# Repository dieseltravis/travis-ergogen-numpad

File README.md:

# travis-ergogen-numpad
A numpad made with Ergogen v4 and SMD components. *Alpha* quality!

## Parts ##

JLCPCB PCBA:
* 17 @ C5184526 Kailh CPG151101S11-1 Mechanical Keyboard Shaft ROHS https://jlcpcb.com/partdetail/Kailh-CPG151101S111/C5184526
* 18 @ C7420318 hongjiacheng 1N4148W SOD-123 Switching Diode ROHS https://jlcpcb.com/partdetail/hongjiacheng-1N4148W/C7420318
* 21 @ C5149201 OPSCO Optoelectronics SK6812MINI-E SMD RGB LEDs(Built-in IC) ROHS https://jlcpcb.com/partdetail/OPSCOOptoelectronics-SK6812MINIE/C5149201
* 21 @ C710467 HUI JU NM1206B104K251CEGN 100nF X7R ±10% 1206 Multilayer Ceramic Capacitors MLCC - SMD/SMT ROHS https://jlcpcb.com/partdetail/HUIJU-NM1206B104K251CEGN/C710467
* C4747954 KNSCHA RST470UF10V029 470uF 10V 260mA@120Hz ±20% SMD,D6.3xL7.7mm Aluminum Electrolytic Capacitors - SMD ROHS https://jlcpcb.com/partdetail/KNSCHA-RST470UF10V029/C4747954

Aliexpress:
* Rotary encoder: EC11 12.5mm 5pcs https://www.aliexpress.us/item/2251832789732148.html
* RP2040 Pro Micro 16M https://www.aliexpress.us/item/3256805943704472.html
* 0.91 Inch OLED Module 0.91" White Blue 128X32 https://www.aliexpress.us/item/3256805787666312.html

Adafruit:
* 2 @ Kailh Mechanical Key Switches - Tactile Brown - 10 pack - Cherry MX Brown Compatible https://www.adafruit.com/product/4954
* Woven USB Cable with USB A to Right Angle USB C https://www.adafruit.com/product/5031

## References ##

* [sadekbaroudi's QMK RGB Matrix configuration](https://github.com/sadekbaroudi/keyboard-guides/blob/master/firmware/qmk/RGB_MATRIX/RGB_MATRIX.md)
* [my first KB](https://github.com/dieseltravis/travis-ergogen-2024/)

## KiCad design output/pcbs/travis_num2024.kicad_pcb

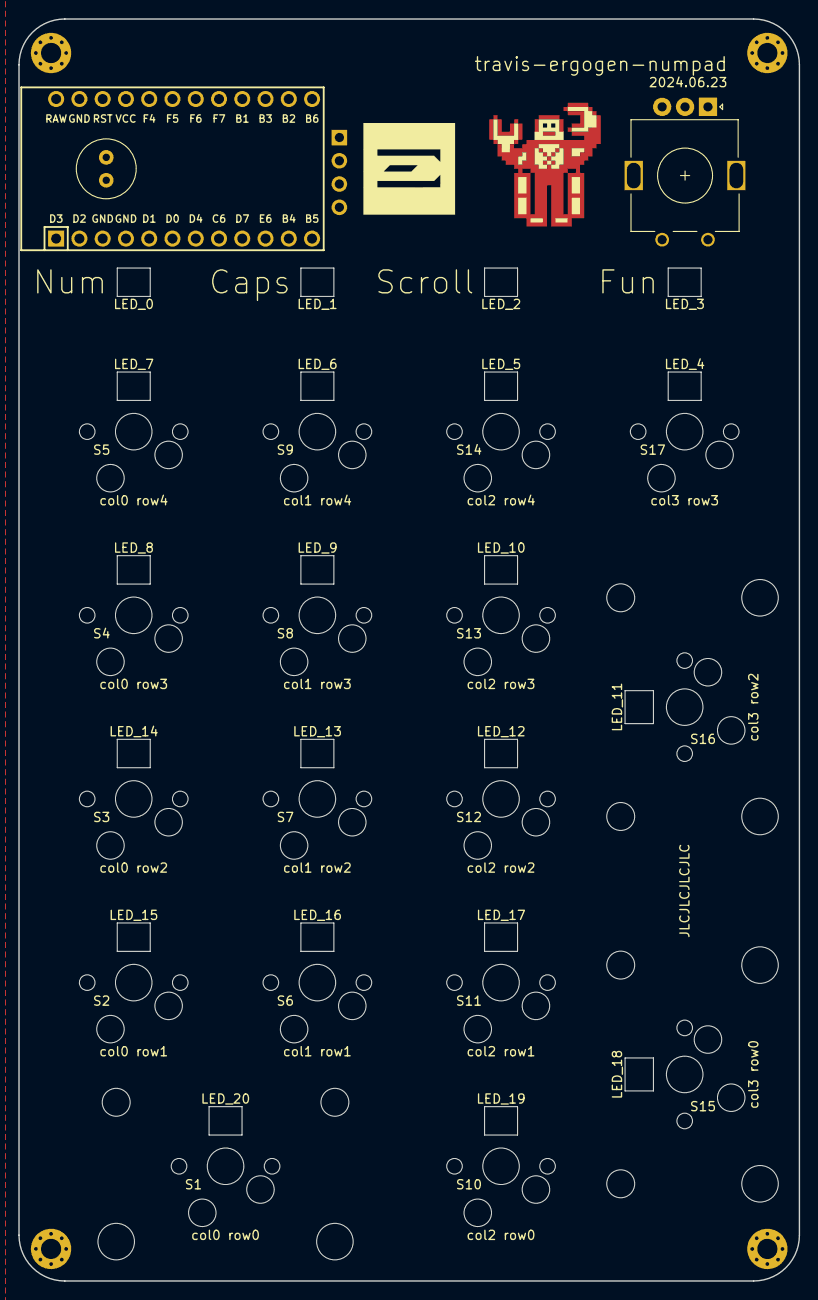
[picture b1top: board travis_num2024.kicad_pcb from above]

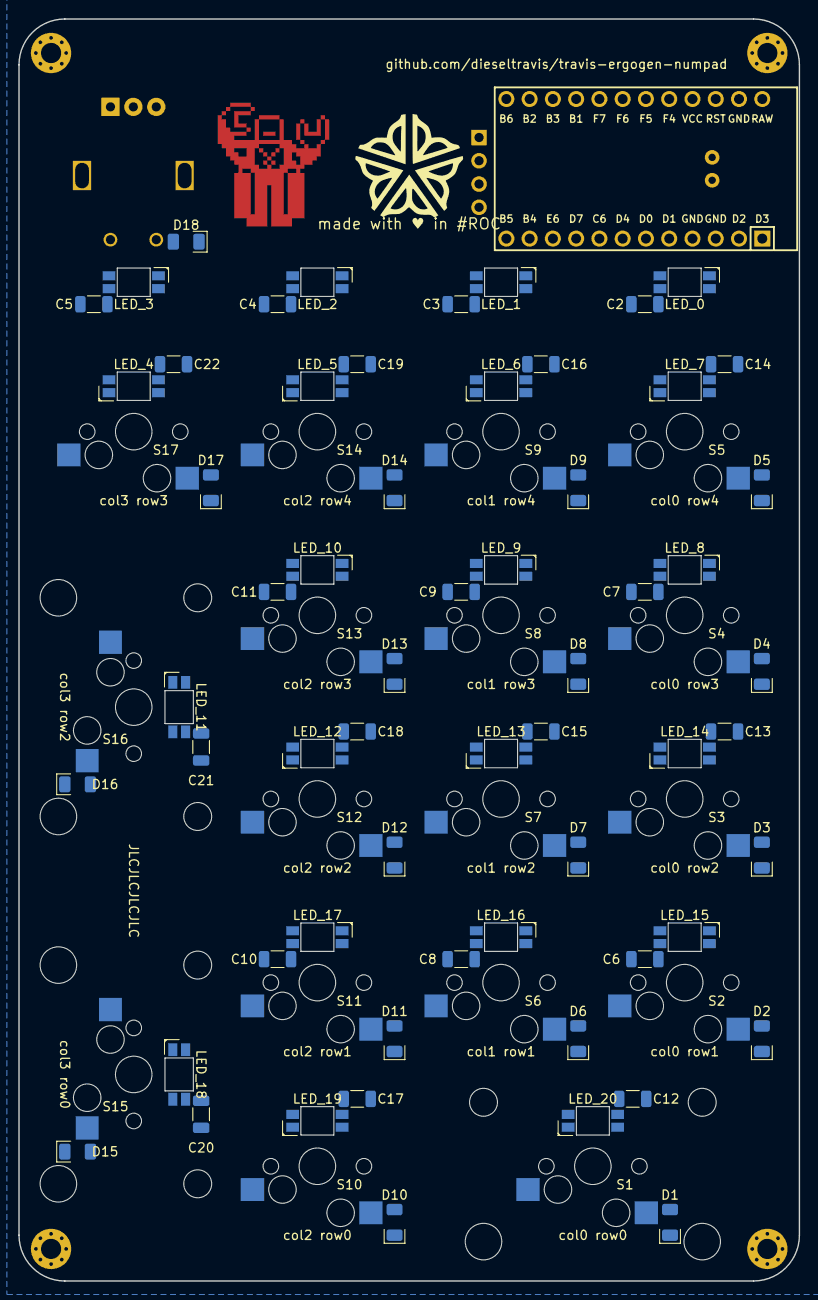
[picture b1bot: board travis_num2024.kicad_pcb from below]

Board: 2 copper layers, 85.2 x 137.8 mm, 91 parts (61 on the bottom side), 54 nets, no tracks yet.

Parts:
C1: 6.3V 1000uF; C_Radial_D6.3mm_H11.0mm_P2.50mm
C2, C3, C4, C5, C6, C7, C8, C9, C10, C11, C12, C13, C14, C15, C16, C17, C18, C19, C20, C21, C22: C_1206_3216Metric
D1, D2, D3, D4, D5, D6, D7, D8, D9, D10, D11, D12, D13, D14, D15, D16, D17, D18: D_1206_3216Metric
HOLE1, HOLE2, HOLE3, HOLE4: MountingHole_2.2mm_M2_Pad_Via
LED1, LED2, LED3, LED4, LED5, LED6, LED7, LED8, LED9, LED10, LED11, LED12, LED13, LED14, LED15, LED16, LED17, LED18, LED19, LED20, LED21: SK6812mini-e; led_SK6812mini-e (per-key, single-side)
LOGO1: utility_ergogen_logo
LOGO2: travis
MCU1: Arduino Pro Micro; Arduino_Pro_Micro
OLED1: OLED; OLED_headers
ROC1: travis
ROT1: EC11; ec11
S1, S2, S3, S4, S5, S6, S7, S8, S9, S10, S11, S12, S13, S14, S15, S16, S17: Kailh MX Switch Sockets; MX
STAB2u1, STAB2u2, STAB2u3: Stabilizer_MX_2.00u

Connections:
GND: C1.2, C2.2, C3.2, C4.2, C5.2, C6.2, C7.2, C8.2, C9.2, C10.2, C11.2, C12.2, C13.2, C14.2, C15.2, C16.2, C17.2, C18.2, C19.2, C20.2, C21.2, C22.2, LED1.3, LED2.3, LED3.3, LED4.3, LED5.3, LED6.3, LED7.3, LED8.3, LED9.3, LED10.3, LED11.3, LED12.3, LED13.3, LED14.3, LED15.3, LED16.3, LED17.3, LED18.3, LED19.3, LED20.3, LED21.3, MCU1.3, MCU1.4, MCU1.23, OLED1.1, ROT1.B
LED_0: LED1.4, MCU1.12
LED_1: LED1.2, LED2.4
LED_2: LED2.2, LED3.4
LED_3: LED3.2, LED4.4
LED_4: LED4.2, LED21.4
LED_5: LED18.4, LED21.2
LED_6: LED15.4, LED18.2
LED_7: LED13.4, LED15.2
LED_8: LED6.4, LED13.2
LED_9: LED6.2, LED8.4
LED_10: LED8.2, LED10.4
LED_11: LED10.2, LED20.4
LED_12: LED17.4, LED20.2
LED_13: LED14.4, LED17.2
LED_14: LED12.4, LED14.2
LED_15: LED5.4, LED12.2
LED_16: LED5.2, LED7.4
LED_17: LED7.2, LED9.4
LED_18: LED9.2, LED19.4
LED_19: LED16.4, LED19.2
LED_20: LED11.4, LED16.2
VCC: C1.1, C2.1, C3.1, C4.1, C5.1, C6.1, C7.1, C8.1, C9.1, C10.1, C11.1, C12.1, C13.1, C14.1, C15.1, C16.1, C17.1, C18.1, C19.1, C20.1, C21.1, C22.1, LED1.1, LED2.1, LED3.1, LED4.1, LED5.1, LED6.1, LED7.1, LED8.1, LED9.1, LED10.1, LED11.1, LED12.1, LED13.1, LED14.1, LED15.1, LED16.1, LED17.1, LED18.1, LED19.1, LED20.1, LED21.1, MCU1.21, OLED1.2
col0: MCU1.20, S1.1, S2.1, S3.1, S4.1, S5.1
col1: MCU1.19, S6.1, S7.1, S8.1, S9.1
col2: MCU1.18, S10.1, S11.1, S12.1, S13.1, S14.1
col3: MCU1.17, ROT1.1, S15.1, S16.1, S17.1
encA: MCU1.14, ROT1.A
encC: MCU1.13, ROT1.C
enc_to: D18.2, ROT1.2
matrix_col0_row0: D1.2, S1.2
matrix_col0_row1: D2.2, S2.2
matrix_col0_row2: D3.2, S3.2
matrix_col0_row3: D4.2, S4.2
matrix_col0_row4: D5.2, S5.2
matrix_col1_row1: D6.2, S6.2
matrix_col1_row2: D7.2, S7.2
matrix_col1_row3: D8.2, S8.2
matrix_col1_row4: D9.2, S9.2
matrix_col2_row0: D10.2, S10.2
matrix_col2_row1: D11.2, S11.2
matrix_col2_row2: D12.2, S12.2
matrix_col2_row3: D13.2, S13.2
matrix_col2_row4: D14.2, S14.2
matrix_col3_row0: D15.2, S15.2
matrix_col3_row2: D16.2, S16.2
matrix_col3_row4: D17.2, S17.2
row0: D1.1, D10.1, D15.1, MCU1.7
row1: D2.1, D6.1, D11.1, MCU1.8
row2: D3.1, D7.1, D12.1, D16.1, MCU1.9
row3: D4.1, D8.1, D13.1, D17.1, MCU1.10
row4: D5.1, D9.1, D14.1, D18.1, MCU1.11
scl: MCU1.6, OLED1.3
sda: MCU1.5, OLED1.4

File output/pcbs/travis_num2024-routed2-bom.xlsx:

Id | Designator | Footprint | Quantity | Designation | JLCPCB Part #（optional）
1 | S5,S14,S2,S17,S3,S8,S15,S6,S11,S12,S1,S9,S10,S7,S13,S16,S4 | MX | 17 | Kailh MX Switch Sockets | C5184526
7 | LED_0,LED_12,LED_5,LED_17,LED_3,LED_15,LED_2,LED_1,LED_7,LED_19,LED_18,LED_8,LE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 | led_SK6812mini-e (per-key, single-side) | 21 | SK6812mini-e | C5149201
8 | C14,C2,C21,C13,C5,C17,C3,C20,C9,C15,C11,C8,C7,C16,C10,C18,C4,C19,C22,C12,C6 | C_1206_3216Metric | 21 | C_1206_3216Metric | C710467
9 | D3,D18,D14,D6,D17,D8,D1,D16,D12,D2,D13,D4,D10,D9,D15,D5,D11,D7 | D_1206_3216Metric | 18 | D_1206_3216Metric | C7420318

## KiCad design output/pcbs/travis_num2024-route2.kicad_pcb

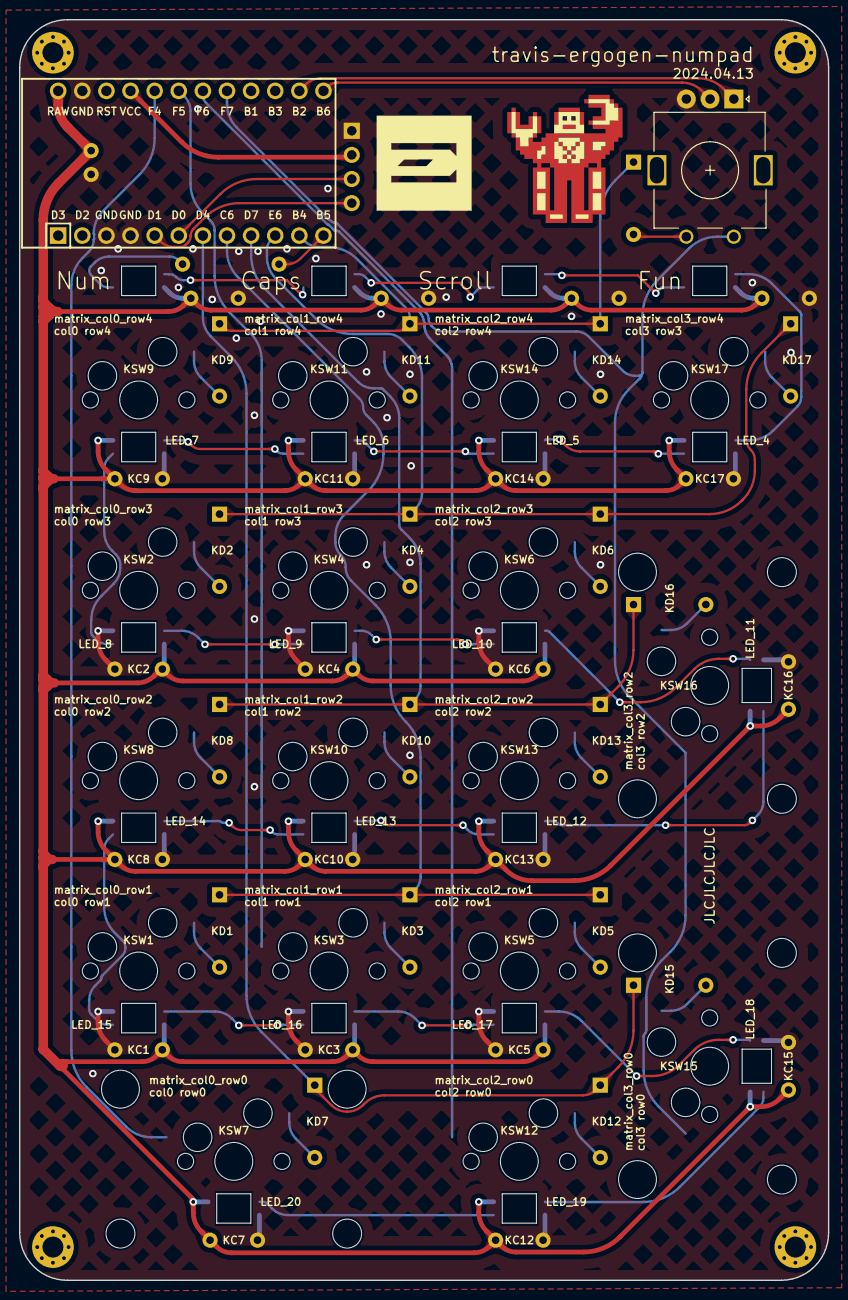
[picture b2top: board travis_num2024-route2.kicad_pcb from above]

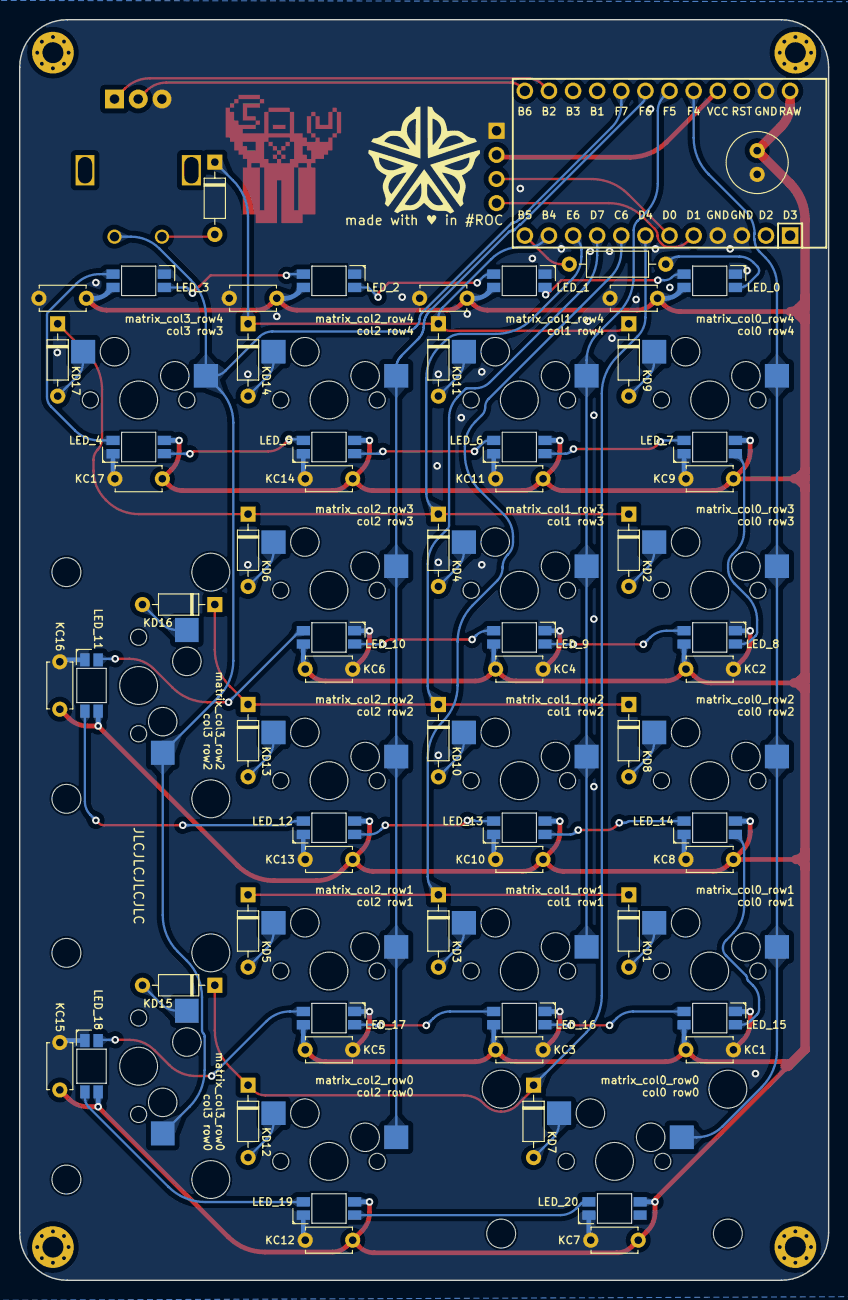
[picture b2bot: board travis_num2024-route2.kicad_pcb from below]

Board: 2 copper layers, 85.2 x 132.8 mm, 92 parts (63 on the bottom side), 56 nets.

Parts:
C1: 6.3V 1000uF; C_Radial_D6.3mm_H11.0mm_P2.50mm
C2, C3, C4, C5: 104; C_Disc_D4.7mm_W2.5mm_P5.00mm
D1: 1N4148; Diode_DO-35
HOLE1, HOLE2, HOLE3, HOLE4: MountingHole_2.2mm_M2_Pad_Via
KC1, KC2, KC3, KC4, KC5, KC6, KC7, KC8, KC9, KC10, KC11, KC12, KC13, KC14, KC15, KC16, KC17: 104; C_Disc_D4.7mm_W2.5mm_P5.00mm
KD1, KD2, KD3, KD4, KD5, KD6, KD7, KD8, KD9, KD10, KD11, KD12, KD13, KD14, KD15, KD16, KD17: 1N4148; Diode_DO-35
KSW1, KSW2, KSW3, KSW4, KSW5, KSW6, KSW7, KSW8, KSW9, KSW10, KSW11, KSW12, KSW13, KSW14, KSW15, KSW16, KSW17: Kailh MX Switch Sockets; MX
LED1, LED2, LED3, LED4: SK6812mini-e; led_SK6812mini-e (per-key, single-side)
LED_4-row3-col3, LED_5-row4-col2, LED_6-row4-col1, LED_7-row4-col0, LED_8-row3-col0, LED_9-row3-col1, LED_10-row3-col2, LED_11-row2-col3, LED_12-row2-col2, LED_13-row2-col1, LED_14-row2-col0, LED_15-row1-col0, LED_16-row1-col1, LED_17-row1-col2, LED_18-row0-col3, LED_19-row0-col2, LED_20-row0-col0: SK6812mini-e; led_SK6812mini-e
LOGO1: ergogen_logo
LOGO2: travis
MCU1: Arduino Pro Micro; Arduino_Pro_Micro
OLED1: OLED; OLED_headers
R1: 470R; R_Axial_DIN0207_L6.3mm_D2.5mm_P10.16mm_Horizontal
ROC1: travis
ROT1: EC11; ec11
STAB2u1, STAB2u2, STAB2u3: Stabilizer_MX_2.00u

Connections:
GND: C1.2, C2.2, C3.2, C4.2, C5.2, KC1.2, KC2.2, KC3.2, KC4.2, KC5.2, KC6.2, KC7.2, KC8.2, KC9.2, KC10.2, KC11.2, KC12.2, KC13.2, KC14.2, KC15.2, KC16.2, KC17.2, LED1.3, LED2.3, LED3.3, LED4.3, LED_4-row3-col3.3, LED_5-row4-col2.3, LED_6-row4-col1.3, LED_7-row4-col0.3, LED_8-row3-col0.3, LED_9-row3-col1.3, LED_10-row3-col2.3, LED_11-row2-col3.3, LED_12-row2-col2.3, LED_13-row2-col1.3, LED_14-row2-col0.3, LED_15-row1-col0.3, LED_16-row1-col1.3, LED_17-row1-col2.3, LED_18-row0-col3.3, LED_19-row0-col2.3, LED_20-row0-col0.3, MCU1.3, MCU1.4, MCU1.23, OLED1.1, ROT1.B
LED: MCU1.12, R1.1
LED_0: LED1.4, R1.2
LED_1: LED1.2, LED2.4
LED_2: LED2.2, LED3.4
LED_3: LED3.2, LED4.4
LED_4: LED4.2, LED_4-row3-col3.4
LED_5: LED_4-row3-col3.2, LED_5-row4-col2.4
LED_6: LED_5-row4-col2.2, LED_6-row4-col1.4
LED_7: LED_6-row4-col1.2, LED_7-row4-col0.4
LED_8: LED_7-row4-col0.2, LED_8-row3-col0.4
LED_9: LED_8-row3-col0.2, LED_9-row3-col1.4
LED_10: LED_9-row3-col1.2, LED_10-row3-col2.4
LED_11: LED_10-row3-col2.2, LED_11-row2-col3.4
LED_12: LED_11-row2-col3.2, LED_12-row2-col2.4
LED_13: LED_12-row2-col2.2, LED_13-row2-col1.4
LED_14: LED_13-row2-col1.2, LED_14-row2-col0.4
LED_15: LED_14-row2-col0.2, LED_15-row1-col0.4
LED_16: LED_15-row1-col0.2, LED_16-row1-col1.4
LED_17: LED_16-row1-col1.2, LED_17-row1-col2.4
LED_18: LED_17-row1-col2.2, LED_18-row0-col3.4
LED_19: LED_18-row0-col3.2, LED_19-row0-col2.4
LED_20: LED_19-row0-col2.2, LED_20-row0-col0.4
RAW: C1.1, C2.1, C3.1, C4.1, C5.1, KC1.1, KC2.1, KC3.1, KC4.1, KC5.1, KC6.1, KC7.1, KC8.1, KC9.1, KC10.1, KC11.1, KC12.1, KC13.1, KC14.1, KC15.1, KC16.1, KC17.1, LED1.1, LED2.1, LED3.1, LED4.1, LED_4-row3-col3.1, LED_5-row4-col2.1, LED_6-row4-col1.1, LED_7-row4-col0.1, LED_8-row3-col0.1, LED_9-row3-col1.1, LED_10-row3-col2.1, LED_11-row2-col3.1, LED_12-row2-col2.1, LED_13-row2-col1.1, LED_14-row2-col0.1, LED_15-row1-col0.1, LED_16-row1-col1.1, LED_17-row1-col2.1, LED_18-row0-col3.1, LED_19-row0-col2.1, LED_20-row0-col0.1, MCU1.24
VCC: MCU1.21, OLED1.2
col0: KSW1.1, KSW2.1, KSW7.1, KSW8.1, KSW9.1, MCU1.20
col1: KSW3.1, KSW4.1, KSW10.1, KSW11.1, MCU1.19
col2: KSW5.1, KSW6.1, KSW12.1, KSW13.1, KSW14.1, MCU1.18
col3: KSW15.1, KSW16.1, KSW17.1, MCU1.17, ROT1.1
encA: MCU1.14, ROT1.A
encC: MCU1.13, ROT1.C
enc_to: D1.2, ROT1.2
matrix_col0_row0: KD7.2, KSW7.2
matrix_col0_row1: KD1.2, KSW1.2
matrix_col0_row2: KD8.2, KSW8.2
matrix_col0_row3: KD2.2, KSW2.2
matrix_col0_row4: KD9.2, KSW9.2
matrix_col1_row1: KD3.2, KSW3.2
matrix_col1_row2: KD10.2, KSW10.2
matrix_col1_row3: KD4.2, KSW4.2
matrix_col1_row4: KD11.2, KSW11.2
matrix_col2_row0: KD12.2, KSW12.2
matrix_col2_row1: KD5.2, KSW5.2
matrix_col2_row2: KD13.2, KSW13.2
matrix_col2_row3: KD6.2, KSW6.2
matrix_col2_row4: KD14.2, KSW14.2
matrix_col3_row0: KD15.2, KSW15.2
matrix_col3_row2: KD16.2, KSW16.2
matrix_col3_row4: KD17.2, KSW17.2
row0: KD7.1, KD12.1, KD15.1, MCU1.7
row1: KD1.1, KD3.1, KD5.1, MCU1.8
row2: KD8.1, KD10.1, KD13.1, KD16.1, MCU1.9
row3: KD2.1, KD4.1, KD6.1, KD17.1, MCU1.10
row4: D1.1, KD9.1, KD11.1, KD14.1, MCU1.11
scl: MCU1.6, OLED1.3
sda: MCU1.5, OLED1.4

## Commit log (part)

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2024-04-07 submod footprint
2024-04-07 initial work
2024-04-09 mcu, leds, spacing
2024-04-10 debug output
2024-04-10 yarn init
2024-04-10 yarn lock
2024-04-10 fixed output
2024-04-10 license
2024-04-10 numpad basic layout
2024-04-11 firmware progress
2024-04-11 layout and label fixes
2024-04-12 roc logo on back
2024-04-13 holes, roc text
2024-04-13 text and cap fixes
2024-04-13 numpad routed, with outputs
2024-04-13 fixed rows, re-routed
2024-04-13 route 1 adjust
2024-04-14 led fix
2024-04-14 qmk firmware functional
2024-04-14 update footprints
2024-04-14 cases
2024-04-14 plate work
2024-04-14 plate 3d
2024-04-14 plate 3d, kle
2024-04-24 working on plate
2024-05-10 updated footprints and ergogen
2024-05-11 new footprints for smd components
2024-05-13 smd progress
2024-05-16 smd progress, labels added
2024-05-17 routed
2024-05-17 clean-up
2024-06-17 kb placer testing
2024-06-22 numpad cap and firmware
2024-06-22 rotated
2024-06-23 added zones, fixed leds, caps
2024-06-24 routed v2
2024-06-25 added qmk led layout & recompiled for ce
2024-07-03 via firmware
2024-07-14 Bump braces in the npm_and_yarn group across 1 directory
    Bumps the npm_and_yarn group with 1 update in the / directory: [braces](https://github.com/micromatch/braces).
    Updates `braces` from 3.0.2 to 3.0.3
    - [Changelog](https://github.com/micromatch/braces/blob/master/CHANGELOG.md)
    - [Commits](https://github.com/micromatch/braces/compare/3.0.2...3.0.3)
    ---
    updated-dependencies:
2024-07-15 partionally functional via
2024-07-23 via works
2024-07-23 fixing volume knob
2024-07-24 indicator lights finally functional
2024-09-10 Bump micromatch in the npm_and_yarn group across 1 directory
    Bumps the npm_and_yarn group with 1 update in the / directory: [micromatch](https://github.com/micromatch/micromatch).
    Updates `micromatch` from 4.0.5 to 4.0.8
    - [Release notes](https://github.com/micromatch/micromatch/releases)
    - [Changelog](https://github.com/micromatch/micromatch/blob/master/CHANGELOG.md)
    - [Commits](https://github.com/micromatch/micromatch/compare/4.0.5...4.0.8)
    ---
2025-03-11 Bump @babel/runtime in the npm_and_yarn group across 1 directory
    Bumps the npm_and_yarn group with 1 update in the / directory: [@babel/runtime](https://github.com/babel/babel/tree/HEAD/packages/babel-runtime).
    Updates `@babel/runtime` from 7.24.5 to 7.26.10
    - [Release notes](https://github.com/babel/babel/releases)
    - [Changelog](https://github.com/babel/babel/blob/main/CHANGELOG.md)
    - [Commits](https://github.com/babel/babel/commits/v7.26.10/packages/babel-runtime)
    ---
2025-11-20 Potential fix for code scanning alert no. 1: Useless regular-expression character escape
2025-11-26 Update devDependencies for dxf and add js-yaml
2025-11-26 yarn update
2025-11-26 Upgrade js-yaml from 3.14.1 to 4.1.1
2026-01-23 Bump lodash in the npm_and_yarn group across 1 directory
    Bumps the npm_and_yarn group with 1 update in the / directory: [lodash](https://github.com/lodash/lodash).
    Updates `lodash` from 4.17.21 to 4.17.23
    - [Release notes](https://github.com/lodash/lodash/releases)
    - [Commits](https://github.com/lodash/lodash/compare/4.17.21...4.17.23)
    ---
    updated-dependencies:
2026-04-06 Bump picomatch in the npm_and_yarn group across 1 directory
    Bumps the npm_and_yarn group with 1 update in the / directory: [picomatch](https://github.com/micromatch/picomatch).
    Updates `picomatch` from 2.3.1 to 2.3.2
    - [Release notes](https://github.com/micromatch/picomatch/releases)
    - [Changelog](https://github.com/micromatch/picomatch/blob/master/CHANGELOG.md)
    - [Commits](https://github.com/micromatch/picomatch/compare/2.3.1...2.3.2)
    ---
2026-04-06 Bump lodash in the npm_and_yarn group across 1 directory
    Bumps the npm_and_yarn group with 1 update in the / directory: [lodash](https://github.com/lodash/lodash).
    Updates `lodash` from 4.17.23 to 4.18.1
    - [Release notes](https://github.com/lodash/lodash/releases)
    - [Commits](https://github.com/lodash/lodash/compare/4.17.23...4.18.1)
    ---
    updated-dependencies:
2026-06-28 Bump js-yaml in the npm_and_yarn group across 1 directory
    Bumps the npm_and_yarn group with 1 update in the / directory: [js-yaml](https://github.com/nodeca/js-yaml).
    Updates `js-yaml` from 4.1.1 to 4.2.0
    - [Changelog](https://github.com/nodeca/js-yaml/blob/master/CHANGELOG.md)
    - [Commits](https://github.com/nodeca/js-yaml/compare/4.1.1...4.2.0)
    ---
    updated-dependencies:
